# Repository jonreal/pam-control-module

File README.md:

# pam-control-module
Hardware/software project for pneumatic artificial muscles (PAM) control module.

After downloading, move libraries/Pam directory to local Arduino libraries/ directory. (0r symlink them).
Flash Arduino with example.ino to run the example code. You will see LEDs light up in sequential order if succesful.

NOTE: current hardware version is missing pulldown resistors on digital input
pins -- this will be fixed in the next version.

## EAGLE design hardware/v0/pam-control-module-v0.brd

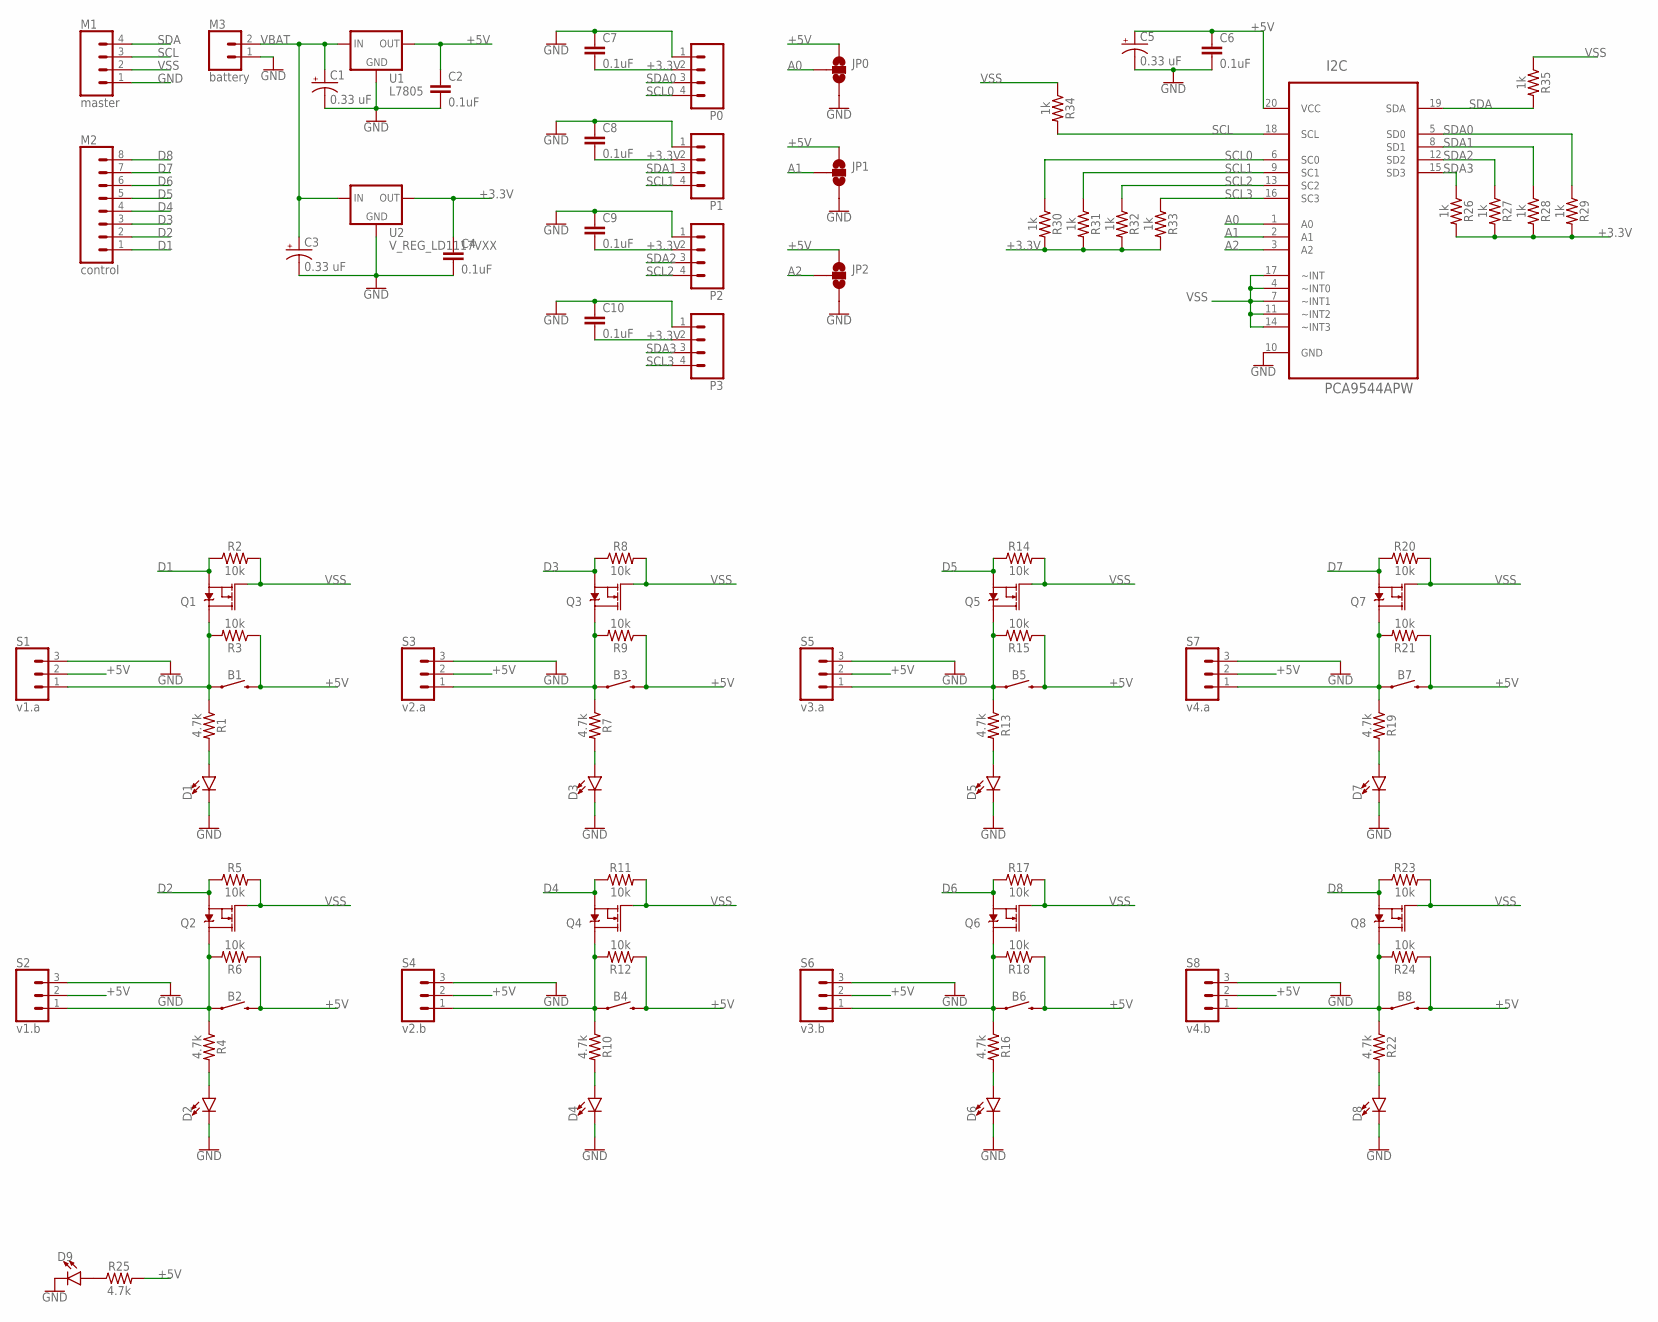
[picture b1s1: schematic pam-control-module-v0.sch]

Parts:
B1, B2, B3, B4, B5, B6, B7, B8: MOMENTARY-SWITCH-SPST-PTH-6.0MM; TACTILE_SWITCH_PTH_6.0MM
C1, C3, C5: 0.33 uF; E2-5
C2, C4, C6, C7, C8, C9, C10: 0.1uF; CAP-PTH-SMALL-KIT
D1, D2, D3, D4, D5, D6, D7, D8, D9: LED3MM; LED_3MM
I2C: PCA9544APW; SOP65P640X120-20N
JP0, JP1, JP2: JUMPER-SMT_3_NO_SILK; SMT-JUMPER_3_NO_SILK
M1: master; 1X04
M2: control; 1X08
M3: battery; 1X02
P0, P1, P2, P3: CONN_04; 1X04
Q1, Q2, Q3, Q4, Q5, Q6, Q7, Q8: MOSFET-NCH-BSS138; SOT23-3
R1, R4, R7, R10, R13, R16, R19, R22, R25: 4.7k; AXIAL-0.3
R2, R3, R5, R6, R8, R9, R11, R12, R14, R15, R17, R18, R20, R21, R23, R24: 10k; AXIAL-0.3
R26, R27, R28, R29, R30, R31, R32, R33, R34, R35: 1k; AXIAL-0.3
S1: v1.a; 1X03
S2: v1.b; 1X03
S3: v2.a; 1X03
S4: v2.b; 1X03
S5: v3.a; 1X03
S6: v3.b; 1X03
S7: v4.a; 1X03
S8: v4.b; 1X03
U1: L7805; 78XXL
U2: V_REG_LD1117VXX; 78XXL

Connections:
+3.3V: C4.1, C7.2, C8.2, C9.2, C10.2, P0.2, P1.2, P2.2, P3.2, R26.P$2 (2), R27.P$2 (2), R28.P$2 (2), R29.P$2 (2), R30.P$2 (2), R31.P$2 (2), R32.P$2 (2), R33.P$2 (2), U2.GND (OUT)
+5V: B1.3 (2), B2.3 (2), B3.3 (2), B4.3 (2), B5.3 (2), B6.3 (2), B7.3 (2), B8.3 (2), C2.1, C5.+, C6.1, I2C.20 (VCC), JP0.1, JP1.1, JP2.1, R3.P$1 (1), R6.P$1 (1), R9.P$1 (1), R12.P$1 (1), R15.P$1 (1), R18.P$1 (1), R21.P$1 (1), R24.P$1 (1), R25.P$2 (2), S1.2, S2.2, S3.2, S4.2, S5.2, S6.2, S7.2, S8.2, U1.OUT
A0: I2C.1 (A0), JP0.2
A1: I2C.2 (A1), JP1.2
A2: I2C.3 (A2), JP2.2
D1: M2.1, Q1.2 (S), R2.P$1 (1)
D2: M2.2, Q2.2 (S), R5.P$1 (1)
D3: M2.3, Q3.2 (S), R8.P$1 (1)
D4: M2.4, Q4.2 (S), R11.P$1 (1)
D5: M2.5, Q5.2 (S), R14.P$1 (1)
D6: M2.6, Q6.2 (S), R17.P$1 (1)
D7: M2.7, Q7.2 (S), R20.P$1 (1)
D8: M2.8, Q8.2 (S), R23.P$1 (1)
GND: C1.-, C2.2, C3.-, C4.2, C5.-, C6.2, C7.1, C8.1, C9.1, C10.1, D1.K (C), D2.K (C), D3.K (C), D4.K (C), D5.K (C), D6.K (C), D7.K (C), D8.K (C), D9.K (C), I2C.10 (GND), JP0.3, JP1.3, JP2.3, M1.1, M3.1, P0.1, P1.1, P2.1, P3.1, S1.3, S2.3, S3.3, S4.3, S5.3, S6.3, S7.3, S8.3, U1.GND, U2.IN (GND)
unnamed: D1.A, R1.P$2 (2)
unnamed: D2.A, R4.P$2 (2)
unnamed: D3.A, R7.P$2 (2)
unnamed: D4.A, R10.P$2 (2)
unnamed: B2.1, Q2.3 (D), R4.P$1 (1), R6.P$2 (2), S2.1
unnamed: D5.A, R13.P$2 (2)
unnamed: D6.A, R16.P$2 (2)
unnamed: D7.A, R19.P$2 (2)
unnamed: D8.A, R22.P$2 (2)
unnamed: D9.A, R25.P$1 (1)
unnamed: B4.1, Q4.3 (D), R10.P$1 (1), R12.P$2 (2), S4.1
unnamed: B6.1, Q6.3 (D), R16.P$1 (1), R18.P$2 (2), S6.1
unnamed: B8.1, Q8.3 (D), R22.P$1 (1), R24.P$2 (2), S8.1
unnamed: B7.1, Q7.3 (D), R19.P$1 (1), R21.P$2 (2), S7.1
unnamed: B5.1, Q5.3 (D), R13.P$1 (1), R15.P$2 (2), S5.1
unnamed: B3.1, Q3.3 (D), R7.P$1 (1), R9.P$2 (2), S3.1
unnamed: B1.1, Q1.3 (D), R1.P$1 (1), R3.P$2 (2), S1.1
SCL: I2C.18 (SCL), M1.3, R34.P$2 (2)
SCL0: I2C.6 (SC0), P0.4, R30.P$1 (1)
SCL1: I2C.9 (SC1), P1.4, R31.P$1 (1)
SCL2: I2C.13 (SC2), P2.4, R32.P$1 (1)
SCL3: I2C.16 (SC3), P3.4, R33.P$1 (1)
SDA: I2C.19 (SDA), M1.4, R35.P$2 (2)
SDA0: I2C.5 (SD0), P0.3, R29.P$1 (1)
SDA1: I2C.8 (SD1), P1.3, R28.P$1 (1)
SDA2: I2C.12 (SD2), P2.3, R27.P$1 (1)
SDA3: I2C.15 (SD3), P3.3, R26.P$1 (1)
VBAT: C1.+, C3.+, M3.2, U1.IN, U2.OUT (IN)
VSS: I2C.4 (~INT0), I2C.7 (~INT1), I2C.11 (~INT2), I2C.14 (~INT3), I2C.17 (~INT), M1.2, Q1.1 (G), Q2.1 (G), Q3.1 (G), Q4.1 (G), Q5.1 (G), Q6.1 (G), Q7.1 (G), Q8.1 (G), R2.P$2 (2), R5.P$2 (2), R8.P$2 (2), R11.P$2 (2), R14.P$2 (2), R17.P$2 (2), R20.P$2 (2), R23.P$2 (2), R34.P$1 (1), R35.P$1 (1)

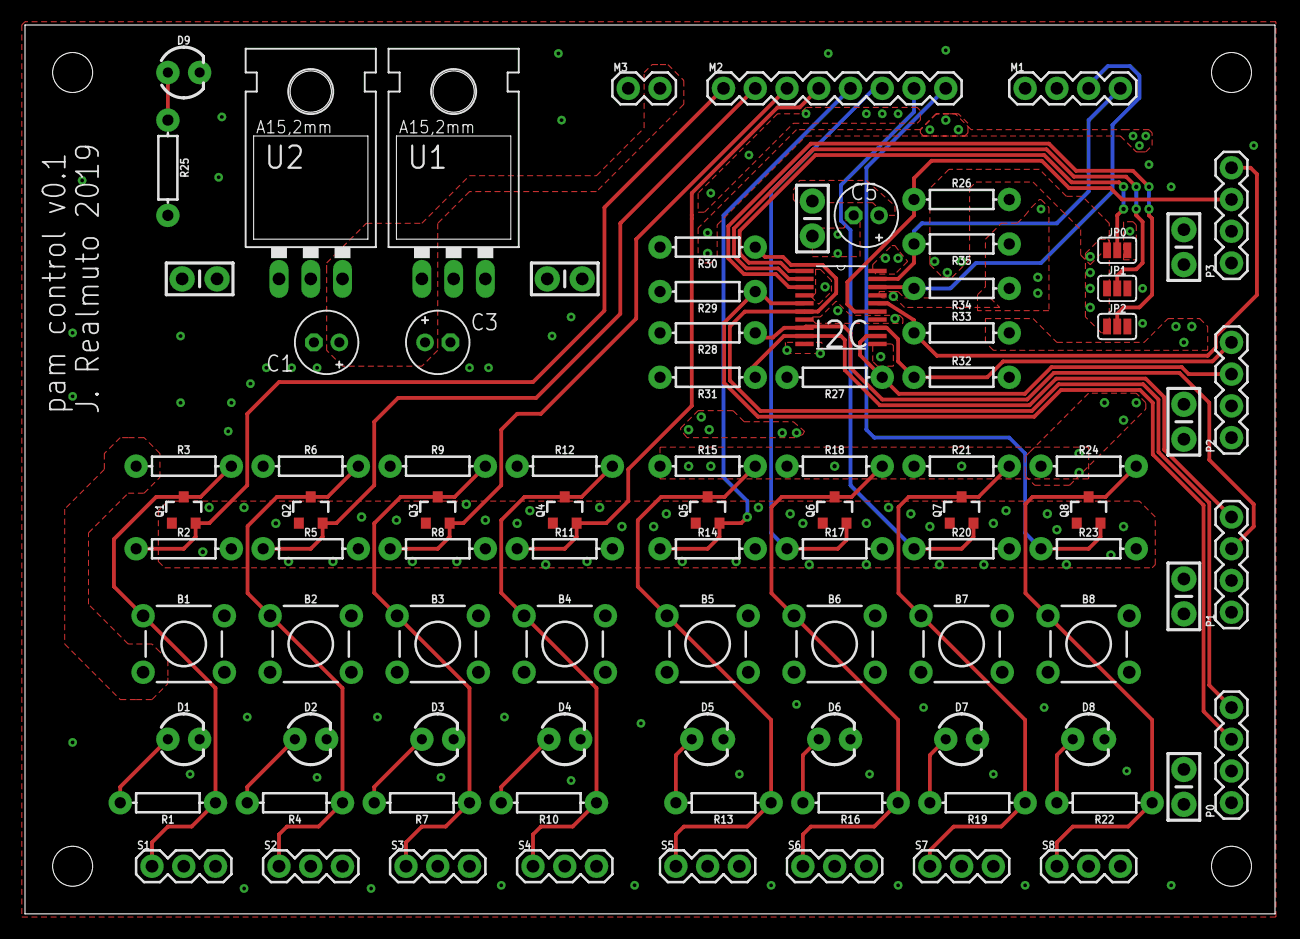
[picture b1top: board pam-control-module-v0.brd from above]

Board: 2 copper layers, 100.0 x 71.1 mm, 91 parts (0 on the bottom side), 43 nets.

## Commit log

2019-03-06 First commit added relevent files
2019-03-06 Removed accidental swap file commit
2019-03-06 Removed comments from a file
2019-03-06 Readme updated
2019-03-06 Added pdf of schematic
2019-05-02 Restructured project files
2019-05-13 reflex based control
2019-06-03 Removed dev sketches
2020-12-15 This is my new file

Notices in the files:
parts and their libraries:
SparkFun-Connectors: Licensing: Creative Commons ShareAlike 4.0 International - https://creativecommons.org/licenses/by-sa/4.0
